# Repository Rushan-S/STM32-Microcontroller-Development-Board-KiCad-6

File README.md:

# STM32 Microcontroller Development Board | KiCad 6

## Project Overview

Designed a custom STM32 ARM Cortex-M microcontroller development board using KiCad 6, covering schematic capture, component selection, circuit design and two-layer PCB layout.

The project focuses on developing a compact embedded development platform with essential microcontroller support circuitry, power management, clock generation, USB connectivity and debugging interfaces.

## Design Features

- Custom STM32 ARM Cortex-M development board.
- Two-layer PCB design.
- Power regulation and decoupling circuitry.
- External crystal clock circuitry.
- USB connectivity.
- SWD programming and debugging interface.
- Boot and reset control circuitry.
- Analog supply filtering.
- Component placement, routing and PCB design rule checks.

## Schematic Design

The schematic includes the microcontroller, power supply, clock generation, USB interface, debugging connections and supporting circuitry.

## PCB Layout and Routing

Designed a two-layer PCB with component placement, signal routing, power distribution and grounding considerations.

## 3D PCB Visualization

The final PCB design was visualized using the KiCad 3D Viewer to inspect component placement and overall board arrangement.

## Hardware Design Considerations

- Component selection and footprint assignment.
- Power regulation and decoupling.
- Signal routing and track management.
- Grounding and power distribution.
- Board outline and mounting holes.
- Design Rule Check (DRC).

## Tools and Technologies

| Category | Tools |
|---|---|
| PCB Design | KiCad 6 |
| Schematic Capture | KiCad Schematic Editor |
| PCB Layout | KiCad PCB Editor |
| 3D Visualization | KiCad 3D Viewer |
| Microcontroller | STM32 ARM Cortex-M |

## Repository Contents

| File | Description |
|---|---|
| `stmdemo.kicad_sch` | KiCad schematic source |
| `stmdemo.kicad_pcb` | PCB layout source |
| `stm32_sch.png` | Schematic visualization |
| `stm32_layout.png` | PCB layout and routing |
| `stmdemo.png` | 3D PCB render |
| `report.txt` | Design report |

## Project Objectives

- Gain practical experience in PCB design and schematic capture.
- Understand microcontroller hardware interfacing.
- Implement essential power and debugging circuits.
- Develop skills in component placement and PCB routing.
- Apply hardware design rules using KiCad.

## Author

**Rushan S**

Electrical and Electronics Engineering

GitHub: [Rushan-S](https://github.com/Rushan-S)

---

*Designed using KiCad 6.*

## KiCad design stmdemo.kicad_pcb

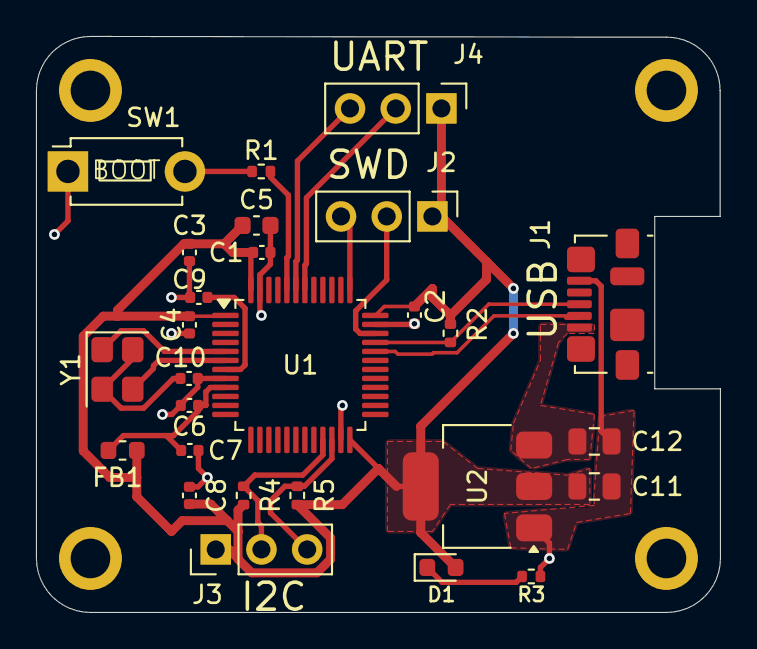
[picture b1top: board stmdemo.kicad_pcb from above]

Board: 2 copper layers, 38.0 x 32.0 mm, 31 parts (0 on the bottom side), 19 nets.

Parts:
C1, C2, C3, C4, C6, C9: 100n; C_0402_1005Metric
C5: 10u; C_0603_1608Metric
C7, C8: 1u; C_0402_1005Metric
C10: 10p; C_0402_1005Metric
C11, C12: 22u; C_0805_2012Metric
D1: RED; LED_0603_1608Metric
FB1: 120R; L_0603_1608Metric
H1, H2, H3, H4: MountingHole_Pad; MountingHole_2.2mm_M2_ISO7380_Pad
J1: USB_B_Micro; USB_Micro-B_Molex_47346-0001
J2, J3, J4: Conn_01x04_Pin; PinHeader_1x03_P2.54mm_Vertical
R1: 10K; R_0402_1005Metric
R2, R3: 1K5; R_0402_1005Metric
R4, R5: 1k5; R_0402_1005Metric
SW1: SW_SPDT; SW_PUSH_1P1T_6x3.5mm_H4.3_APEM_MJTP1243
U1: STM32F103C8Tx; LQFP-48_7x7mm_P0.5mm
U2: AMS1117-3.3; SOT-223-3_TabPin2
Y1: 16MHz; Crystal_SMD_3225-4Pin_3.2x2.5mm

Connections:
+3.3V: C1.1, C2.1, C3.1, C4.1, C5.1, C8.1, C11.1, D1.2 (A), FB1.1, J2.1, J3.1, J4.1, R2.1, R4.1, R5.1, U1.1 (VBAT), U1.24 (VDD), U1.36 (VDD), U1.48 (VDD), U2.2 (VO)
+3.3VA: C6.1, C7.1, FB1.2, U1.9 (VDDA)
/BOOTO: R1.2, U1.44 (BOOT0)
/HSE_IN: U1.5 (PD0), Y1.1
/HSE_OUT: U1.6 (PD1), Y1.3
/I2C2_SCL: J3.2, R4.2, U1.21 (PB10)
/I2C2_SDA: J3.3, R5.2, U1.22 (PB11)
/NRST: C9.1, U1.7 (NRST)
/SWCLK: J2.3, U1.37 (PA14)
/SWDIO: J2.2, U1.34 (PA13)
/SW_BOOT: R1.1, SW1.2 (B)
/USART1_RX: J4.3, U1.43 (PB7)
/USART1_TX: J4.2, U1.42 (PB6)
/USB_D+: J1.3 (D+), R2.2, U1.33 (PA12)
/USB_D-: J1.2 (D-), U1.32 (PA11)
GND: C1.2, C2.2, C3.2, C4.2, C5.2, C6.2, C7.2, C8.2, C9.2, C10.2, C11.2, C12.2, J1.5 (GND), R3.2, SW1.1 (A), U1.8 (VSSA), U1.23 (VSS), U1.35 (VSS), U1.47 (VSS), U2.1 (GND)
unnamed: C10.1, Y1.2 (G), Y1.4 (G)
unnamed: D1.1 (K), R3.1
VBUS: C12.1, J1.1 (VBUS), U2.3 (VI)
